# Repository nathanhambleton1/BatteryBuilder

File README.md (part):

# Battery Builder

A MATLAB app for lithium-ion cell test data. It has three tabs:

| Tab | What it does |
|---|---|
| **Plot** | Look at the test: cursor read-out, fit buttons, drag-to-zoom, middle-mouse pan. |
| **Load profile** | Shows the test's current profile and saves it to the workspace for a Simulink *Controlled Current Source*. |
| **Modeling** | One button pulls every parameter it can out of the test and fills in the boxes for the Simscape **Battery (Table-Based)** block. Empty boxes tell you what you still need from the datasheet. A second button saves everything to the workspace. |

Building the Simulink model is up to you; this app produces the workspace variables it needs. **Extract** fits the tables to the whole test so that a Battery (Table-Based) block reproduces it: on the sample 0 °C file **20 mV rms** in Simulink, the right starting voltage, and every discharge stopping at the cut-off. See §14.

**Presentation + video:** [`Modeling_Tab_Presentation.pptx`](Modeling_Tab_Presentation.pptx) (66 slides, Century Gothic, MATLAB charts as movable pictures, speaker notes) and [`Modeling_Tab_Presentation.mp4`](Modeling_Tab_Presentation.mp4) (the same deck presented with a voice-over, about an hour) explain how every Modeling-tab value is calculated from the charge and discharge cycles, why each method was chosen, and how to set up the thermal mass and h·A for the Simulink convection block. See §13.

---

## 1. Quick start

```matlab
cd 'C:\App Projects\BatteryBuilder'
BatteryDataBuilder                    % opens the app
BatteryDataBuilder('cell_25C.csv')    % opens it with a file already loaded
```

1. **Open CSV...** → pick one test file (one cell; charges at 25 °C, discharges at the test temperature).
2. **Plot** tab: look at the data.
3. **Load profile** tab: **Save load profile to workspace** → `batt_load`, `batt_stopTime`, `batt_Ts`, `batt_ambient`.
4. **Modeling** tab: **1. Extract data from test**. Fill in any orange *Required* boxes from the datasheet, then **2. Save to workspace** → `batt_*`.
5. In Simulink, type the `batt_*` names into the Battery (Table-Based) block (hover over any box to see where each one goes).

Requirements: MATLAB R2021a or newer. No toolboxes are needed for the app itself. Simscape Battery (or Simscape Electrical) is only needed for the Simulink model you build afterwards.

---

## 2. Files

```
BatteryDataBuilder.m              <- the app. Builds the window and the three tabs.
src/
  plotTab.m                   Tab 1 - interactive plot
  loadProfileTab.m            Tab 2 - current profile -> workspace
  modelingTab.m               Tab 3 - parameter boxes, Extract / Save buttons
  blockParameterList.m        the list of boxes on Tab 3 (variable names, where they go, datasheet hints)
  extractCellParameters.m     all the calculations (capacity, SOC, OCV, R0, RC pairs, thermal)
  explainParameter.m          the "How?" pop-up windows
  batterySources.m            the published sources behind each method (links shown in the "How?" windows)
  fitTableBased.m             Extract step 2: the tables fitted to the whole test (one least-squares solve) - §14
  simulateTableBased.m        the Table-Based block's equations in plain MATLAB (the fit and "Fit vs data")
  refineTimeGrid.m            splits long sample intervals (<= 0.2 % SOC) so the fit integrates like Simulink
  showTableFit.m              the "Fit vs data" window
graphs/                       PNGs: C-rate graphs (Load profile tab) and the fit check
plots/                        PNGs saved by the Plot tab's "Copy plot to a figure"
  loadBatteryCsv.m            reads a cycler CSV
Modeling_Tab_Presentation.pptx   the presentation (§13)
Modeling_Tab_Presentation.mp4    the presentation, narrated (§13)
```

`BatteryDataBuilder.m` adds `src/` to the path itself, so you never need to touch the other files to use the app.

How the pieces talk to each other:

```
BatteryDataBuilder.m
   | Open CSV  -> loadBatteryCsv(file) -> d (dataset)
   |              d is handed to every tab: plotTab.setData(d), loadProfileTab.setData(d), modelingTab.setData(d)
   |
   +-- plotTab          (only displays d)
   +-- loadProfileTab   (d.t, d.I, d.Tch -> batt_load, batt_stopTime, batt_Ts, batt_ambient)
   +-- modelingTab      Extract -> extractCellParameters(d, nRC, SOC_vec) -> R
                        R fills the boxes; "How?" -> explainParameter(key, R)
                        after Extract, d gains a 'SOC (-)' column which is sent back to the Plot tab
```

---

## 3. Test data format

One CSV per test. Column names are matched loosely (case, spaces and punctuation are ignored) and their order does not matter:

```
Record#  Step  TestTime (s)  StepTime (s)  Capacity (Ah)  Energy (Wh)
Current (A)  Voltage (V)  State  ES  DateTime  Temp 1  Chamber Temperature (C)
```

| Column | Used for |
|---|---|
| TestTime (s) | time axis (`DateTime` is the fallback). `hh:mm:ss` and `1d 02:03:04` strings are accepted. |
| Current (A), Voltage (V) | everything |
| State (C / D / R) | sign of the current when the cycler logs a positive magnitude, and rest detection |
| StepTime (s) | the exact moment the current switched, for R0 and the RC fits |
| Temp 1 | cell temperature: thermal fit and initial temperature |
| Chamber Temperature (C) | ambient for the thermal fit (and `batt_ambient`), and the test temperature label: the median chamber temperature **during the discharges** (§7.0) |

### Current sign: positive = charge

Everywhere in the app, and in every saved variable, **positive current = charge (into the cell) and negative = discharge**. The loader works out which way round your file is:

* If there is a State column, it compares the sign of the current in C and D rows, or uses State to give a sign to a magnitude-only current.
* If there is no State column, charging current must make the voltage rise (checked with dV/dt).

The top bar of the app shows which case was found (e.g. *"magnitude in file, sign taken from the State column"*).

---

## 4. Tab 1: Plot

| Control | Action |
|---|---|
| X axis / Left Y / Right Y | Pick columns. Ctrl+click picks several. A right axis is shown when something is selected there. Changing any of them redraws and fits the view to every curve straight away. **(none)** at the top of a Y list leaves that axis empty. |
| **Load twin from workspace** | Adds the digital-twin signals at the bottom of both Y lists, under a separator (see below). Press again after a new simulation run. |
| **Same units -> same Y scale** | On by default. When every curve on the left **and** the right has the same unit, both Y axes get the same limits, so e.g. measured voltage (left) and twin voltage (right) lie on top of each other. The lock holds through every zoom, pan and fit. The box shows `(locked: V)`, or `(units differ)` when it cannot apply. Untick it to give each side its own scale again. |
| **Fit all** | Show all the data. |
| **Fit horizontal** | Full X range, keep the Y zoom. |
| **Fit vertical** | Fit Y to the data inside the X range you are looking at. |
| Drag drop-down | Left-drag zooms to a box, X only, Y only, or is off. |
| **Left-drag** | Zoom into the dragged box. |
| **Middle-drag** (or Shift+left-drag) | Pan (move the view around). |
| Scroll wheel | Zoom in / out around the mouse. |
| Double-click | Fit all. |
| Right-click / **Zoom back** | Undo the last zoom or pan. |
| **Cursor** | A vertical line follows the mouse. Every curve gets a marker where the line crosses it, with its value in a label right next to the crossing. Labels move up and down with the curves, are pushed apart when they would overlap, and flip to the left side near the right edge. If the X column goes back and forth (e.g. Voltage vs SOC), the nearest point on screen is used instead. |
| **Copy plot to a figure** | A normal MATLAB figure of the current view, for saving or printing (legend bottom-left). It is also saved straight away as `plots/<csv name>.png` (overwritten by the next copy of the same file). |
| Keys | `f` = fit all, `Backspace` = zoom back, `Esc` = cancel a drag. |

### Twin vs measured

Log the twin with To Workspace blocks named `twin_soc`, `twin_current`, `twin_voltage` and `twin_temp` (format **Timeseries** or **Structure With Time**; *Array* also works together with `tout`). They are read from the base workspace, or from `out` when the model uses "Single simulation output". They show up as `Twin: SOC (-)`, `Twin: Current (A)`, `Twin: Voltage (V)`, `Twin: Temp (°C)`, drawn dashed. The twin's time starts at 0 like `batt_load`, so it lines up with the test on any X column (time columns are extended past the end of the test). A temperature above 150 is taken to be kelvin and converted to °C; an SOC above 1.5 is taken to be percent.

Each twin signal has a measured partner: SOC ↔ `SOC (-)` (after Extract), current ↔ `Current, +charge (A)`, voltage ↔ the file's voltage column, temperature ↔ the cell temperature column (`Temp 1`). With both shown and the **Cursor** on, a yellow label on the other side of the cursor line shows `Δ = twin − measured` at the cursor position. When there is no room on that side (the cursor is near an edge), the label moves below the value labels instead.

**Comparing twin and measured.** Two ways, both on one scale:
* Put both in the **same** list (Ctrl+click), e.g. `Voltage (V)` and `Twin: Voltage (V)` on the left. That leaves the right axis free for something else, such as current.
* Or put one on each side, e.g. `Voltage (V)` left and `Twin: Voltage (V)` right. With **Same units -> same Y scale** ticked, the right axis copies the left one.

The unit is the text in the last brackets of the name (`Voltage (V)` → V); the temperature columns count as °C. A twin signal counts as having its measured partner's unit, so `Temp 1` and `Twin: Temp (°C)` lock together too (`unitKey`, `updateLock` in `plotTab.m`).

Extra columns added for plotting: `Test Time (h)`, `Current, +charge (A)`, `Power, +charge (W)`, `Net Ah in (Ah)`, and after an extraction `SOC (-)`.

The tab keeps **one** axes for its whole life, with both Y axes created up front; the right ruler is only hidden when nothing is picked for it. On every change the old lines are deleted, the new ones drawn, the view fitted, and ~0.25 s later the limits are applied once more and the axes repainted (`refreshPlot`, `repaintSoon`). Earlier versions deleted and re-created the axes on each change, which sometimes left the right-axis curves undrawn until a click or **Fit all** forced a repaint.

Pan is implemented in `plotTab.m` → `onMouseDown` (`SelectionType == 'extend'`, which is what MATLAB reports for the middle button) and `onMouseMove`, which turns the mouse movement in pixels into data units using the axes' size in pixels.

---

## 5. Tab 2: Load profile

The plot shows the current over the whole test: green = charge (+), orange = discharge (−).

**Save load profile to workspace** writes:

| Variable | Contents |
|---|---|
| `batt_load` | `[t I]`, N×2. Time in seconds from 0, current in A, **+ = charge**. |
| `batt_load_ts` | the same data as a `timeseries` |
| `batt_stopTime` | length of the test (s): set the model **Stop time** to `batt_stopTime` |
| `batt_Ts` | the test's sampling interval (s, the median spacing of the time stamps): use it as the To Workspace **Sample time** (or a fixed-step solver's step size) so the twin is logged like the real test |
| `batt_ambient` | `[t T]`, N×2: the **chamber temperature in kelvin** on the same time points as `batt_load`, for the battery's thermal port. Missing readings are bridged linearly. Not written (and the list says why) if the file has no chamber temperature column. |
| `batt_ambient_ts` | the same as a `timeseries` |

The list under the button shows these values, plus the test's shortest and longest logging interval (cyclers often log faster during pulses than during rests, which is why the median is used).

### Pulse labels

Every charge and discharge pulse (a run of current with one sign) is labelled with:

* its **C-rate**, `|I| / AH`: the level it spends most of its time at (`CC`), the CC current of a tapering charge (`CC-CV`), or the average and peak for a varying load (`avg …C, max …C`);
* the **Ah** that went in (`+`) or came out (`−`) during that pulse: `Σ I·Δt / 3600`.

The C-rate needs the capacity: press **Extract** on the Modeling tab (or type an AH there) and the labels update. Until then the labels show amps. Labels that would overlap are hidden, biggest pulses first; zoom in to see the rest (`findPulses`, `layoutLabels` in `loadProfileTab.m`).

### Using it in Simulink

```
From Workspace  ->  Simulink-PS Converter  ->  Controlled Current Source  ->  Battery (Table-Based)
 Data: batt_load       output unit: A           + (arrow head) -> battery +
 Interpolate: on                                -               -> battery -
 Final value: Holding final value
```

With the source wired head-to-battery-plus, a positive signal pushes current **into** the battery, which is charging. That matches the sign of `batt_load`.

Thermal port (block option *Thermal model* = lumped thermal mass):

```
From Workspace  ->  Simulink-PS Converter  ->  Controlled Temperature Source  ->  Convective Heat Transfer  ->  Battery port H
 Data: batt_ambient    output unit: K           port A -> Thermal Reference        Area = 1 m^2
 Interpolate: on                                port B -> Convective block A       coefficient = batt_hA
```

Kelvin is used so the Simulink-PS Converter needs no affine (°C) conversion. A chamber that holds one temperature makes `batt_ambient` almost flat, but it still carries the real drift of the test, which the thermal fit (§7.7) used too.

Every logged current holds until the next sample, exactly like the cycler's own Ah counter. `buildProfile` (in `loadProfileTab.m`) therefore inserts one extra point 1 ms before **every** change of current, carrying the *old* current. With *Interpolate data = on*, the signal then steps exactly like the real test instead of ramping between two samples. (Ramping through the tapering current of a CV charge used to add 0.14 % SOC per charge in Simulink, §14.2.)

---

## 6. Tab 3: Modeling

### The walk-through

1. **1. Extract data from test**: runs `extractCellParameters` on the loaded file. Every box it can calculate turns green (**✓ From data**).
2. Boxes it could not calculate stay empty:
   * **Required** (orange): the block needs it. Type it in from the datasheet.
   * **Optional** (grey): leave it empty if you don't have it.
   * Hover over the status to see *why* it could not be found (e.g. *"no cell temperature column in the file"*) and what to look for on the datasheet.
3. Any box can be typed into: a number, a vector like `[0.02 0.021 0.022]`, or `0:0.1:1`. Typed values show as **Entered by you** (blue) and are never overwritten by Extract.
4. **How?** (on green boxes) opens a window that walks through the calculation step by step: what the parameter means in the block, the equations (rendered in LaTeX), the actual numbers from your file plugged into them (a worked example), the final table, and plots of the data it came from.
   A box whose cross-check failed shows **⚠ Check** instead of ✓ (e.g. AH vs the cycler's own Capacity column, or SOC0 vs the voltage).
5. **2. Save to workspace** writes every filled box as its `batt_*` variable and tells you which required boxes are still empty.

**Hover over any box** to see its workspace variable name and exactly where it goes in the block dialog.

### Block set-up this app assumes

These options stay the same as before; set them once in the block dialog:

| Block option | Setting |
|---|---|
| Charge dynamics | the **Charge dynamics (RC pairs)** drop-down on the tab (1, 2 or 3; default 3, the third pair is the hours-long recovery after a discharge, §14). Saved as `batt_nRC`. |
| Tabulate parameters over temperature | **Yes** when the file has two temperatures (charges at 25 °C, discharges at T ≠ 25 °C): Vector of temperatures T = `batt_T_vec` (K), and V0, R0, R1.., tau1.. are SOC × T matrices. **No** for the 25 °C file (one temperature, the tables are vectors). The tab shows which one. |
| Current directionality | **No** |
| Thermal port | **Model** |
| Expose SOC port | **Yes** |
| Self-discharge | Disabled. Enable it only if you fill in `batt_Rleak`. |
| Fade / calendar aging | Disabled |
| Extrapolation method | Nearest |

### The boxes

| Box | Variable | Block dialog | From the data? | If not: datasheet |
|---|---|---|---|---|
| SOC breakpoints | `batt_SOC_vec` | Main › Vector of state-of-charge values | your choice (default 31 points, dense at the knee and the top: `[0 .005 .01 .02 … .05 .075 .1:.05:.9 .925 .95 .97 .98 .99 1]`) | n/a |
| Temperature breakpoints T | `batt_T_vec` | Main › Vector of temperatures, T (K) | the chamber during the discharges and during the charges, when they differ by > 3 K (§7.0) | n/a (empty = one temperature) |
| Open-circuit voltage V0(SOC,T) | `batt_V0_vec` | Main › Open-circuit voltage, V0(SOC,T) | zero-current line through the discharges at several rates; long rests at the two ends | OCV-vs-SOC curve. **Required.** |
| Terminal voltage range | `batt_V_range` | Main › Terminal voltage operating range [Min Max] | min / max measured | cut-off voltages. Optional. |
| Terminal resistance R0(SOC,T) | `batt_R0_vec` | Main › Terminal resistance, R0(SOC,T) | first sample after each step from a rest | DC internal resistance. **Required.** |
| Cell capacity AH | `batt_AH` | Main › Cell capacity, AH (A*hr) | full CC-CV → discharge to cut-off | rated capacity. **Required.** |
| Self-discharge resistance | `batt_Rleak` | Main › Self-discharge resistance, Rleak | never (needs weeks of storage) | Optional |
| R1..R3(SOC,T), tau1..tau3(SOC,T) | `batt_R1_vec`, `batt_tau1_vec`, ... | Dynamics › polarization resistance / time constant | the first minutes after each step from a rest; R scaled to the measured R_dc at the other SOCs | rarely published. **Required** for the pairs in use. |
| Thermal mass | `batt_thermal_mass` | Thermal › Thermal mass (J/K) | cell temperature self-heating | mass × specific heat. **Required.** |
| Convection h·A | `batt_hA` | *not a battery parameter*: Convective Heat Transfer block, Area = 1 m², coefficient = `batt_hA` | cell temperature self-heating | depends on your fixture. Optional. |
| Initial SOC | `batt_SOC0` | Initial Targets › State of charge | SOC at the first sample | Optional |
| Initial cell temperature | `batt_T0` | Initial Targets › Cell temperature (K) | first cell-temperature reading | Optional |

A single number typed into an SOC-table box (e.g. one datasheet resistance) is copied to every SOC point when saved.

### What "no guessing" means here

* A box is only filled from the data if the data really contains what that value needs. Otherwise it stays empty and says why.
* There are **no** built-in default values. The old version's "assumed" fallbacks are gone.
* A capacity you type in is only used to build the SOC axis when the test has no complete full-to-empty discharge. The AH box then still shows **Entered by you**, not "From data".
* Between two measured SOC points a table is linearly interpolated. Beyond the measured SOC range the end value is held, which is what the block's *Nearest* extrapolation would do anyway. Every table entry is labelled in its **How?** window: `M` measured near that SOC, `I` interpolated, `E` end value held, `S` R1..R3 scaled so R0 + ΣR_k equals the R_dc measured at that SOC (§7.5). R0 itself is never scaled.
* Points taken while the cell was more than 3 K away from the chamber temperature (e.g. right after the 5.8C discharge) are left out of the tables: they belong to a different temperature.
* The OCV table is only filled if the data covers the whole SOC range. Past the data it extends at most 0.01 SOC.

---

## 7. How each value is calculated

All of this is in `src/extractCellParameters.m`, in the same order as below. Every method is tied to published work or MathWorks documentation; the tags in square brackets, such as [INL15], point to the reference list in §12. The same sources are listed, with links, at the bottom of every **How?** window (`src/batterySources.m`).

### 7.0 The model, and what your test can measure

The Battery (Table-Based) block [MW-TB], built on [Huria12], is an equivalent circuit: an OCV source, a series resistance R0 and up to three RC pairs, all as tables over SOC. Written with *i* = discharge current (positive):

```
V        = V0(SOC) − i·R0(SOC) − Σ_k R_k(SOC)·x_k        terminal voltage
dx_k/dt  = (i − x_k) / tau_k(SOC)                         current through RC pair k's resistor
SOC      = SOC0 − ∫ i dt / (3600·AH)                       coulomb counting
m·cp · dT/dt = i²·R0 + Σ_k R_k·x_k² − h·A·(T − T_amb)      lumped thermal mass + convection
```

**Your test** is a rate test of about 70 h: 5 CC-CV charges and 5 discharges to the cut-off, with rests in between. Most files use 0.1C, 0.2C, 0.5C and 1C, then one fast discharge that varies from about 3C to 7C:

```
0.34C CC-CV charge → 0.1C discharge to cut-off → 0.34C CC-CV → 0.2C → 0.34C CC-CV → ~0.5C
                   → 0.34C CC-CV → 1C → 0.34C CC-CV → ~3-7C          (with rests in between)
```

**The chamber schedule.** One file = one test temperature T, but the chamber is not at T all the time:

```
25 °C : rest → CC-CV charge
   T  : (right after the charge) rest → discharge
25 °C : (right after the discharge) rest → next charge ...            and so on, 5 times
```

So every **discharge** runs at the file's temperature T and every **charge** runs at 25 °C. What that means for the extraction:

* **Test temperature label** (`d.T_C`, what the tables are "for") = the median chamber temperature over the *discharge* samples. The median over the whole file can land on 25 °C for a cold test, because about half the test is at 25 °C (`loadBatteryCsv.m`). The top bar says so when the chamber moves by more than 3 K.
* **Two table temperatures.** In a file that is not at 25 °C the tables are built at **both** chamber temperatures (`d.T_C` for the discharges, `d.T_chg_C` for the charges), each from the data taken with the cell within ±3 K of it (§7.10 `maxDT`). They are saved as SOC × T matrices with `batt_T_vec = [T_low T_high] + 273.15` K, for the block option *Tabulate parameters over temperature = Yes*. `extractCellParameters` runs the table part once per temperature; `R.byT{j}` is the full result for `T_vec(j)`, and every **How?** window for a table opens once per temperature.
  * **Test temperature (discharges):** R0 and the RC pairs from the start of each discharge (SOC 1, after the 3 h rest at T), OCV and R_dc from the discharges at several rates. AH, SOC, SOC0 and the thermal values come from here too (AH is one number in the block).
  * **25 °C (charges):** R0 and the RC pairs from the start of each charge (near SOC 0, after the rest back at 25 °C), R_dc from the CC part of the charges (§7.5). There are no discharges at 25 °C, so V0 at 25 °C is the test temperature's V0 (the OCV changes only a few mV over 25 K). A table that cannot be measured at one temperature is copied from the other one so the block gets a full matrix, and its note says **COPIED**.
* **In the 25 °C file** everything is at 25 °C: one temperature, and the steps from rest at SOC 1 (discharges) and near SOC 0 (charges) both count.
* **What is NOT used: the rests after a step.** After a discharge the chamber goes back to 25 °C straight away, so the cell warms by ~25 K during that rest; after a charge it cools to T. The relaxation there is mixed with the temperature change, and fitting RC pairs to it gave nonsense (R1 of ~900 mΩ, tau at its 3000 s limit, worse with every extra pair). The start of each step is taken after a 3 h rest at a steady temperature, sampled from 0.05 s on, so that is where the dynamics are measured.
* **Thermal fit and `batt_ambient`** use the chamber column as it is, steps and all, so the 25 ↔ T switching is in the heat balance and in the Simulink ambient. `batt_T0` is the first cell reading (≈ 25 °C, because the chamber starts at 25 °C), which is the right start for a simulation driven by `batt_ambient`.

That decides what can be measured, and where:

| Quantity | Where this test shows it | How (section) |
|---|---|---|
| AH | every discharge from FULL to the cut-off; the slowest one (0.1C) is used | 7.2 |
| SOC | everywhere, by coulomb counting from FULL | 7.3 |
| OCV | **the whole SOC range**: the same discharge at 4 rates is extrapolated to zero current | 7.6 |
| R_dc = R0 + R1 + R2 | **the whole SOC range**: the slope of the same fit | 7.6 |
| R0 on its own | only where the current **starts from a rest**: each discharge (SOC 1, at T), each charge (SOC ≈ 0 … 0.03, at 25 °C) | 7.4 |
| R1, R2, tau1, tau2 on their own | the first minutes after those same steps | 7.5 |
| m·cp, h·A | the 5.8C discharge heats the cell, which then cools in the rest | 7.7 |

So in the middle of the SOC range the **sum** R0 + R1 + R2 is measured, but not how it splits between them: the current never starts from a rest there. The tables are built to respect that (§7.5, the `S` flag), and nothing is filled in from outside the file.

### 7.1 Phases
The current is split into runs of **charge** (I > 0), **discharge** (I < 0) and **rest** (I = 0). Back-to-back steps of the same kind merge, so a CC step plus a CV step is one charge phase (`findPhases`).

A charge phase is a **CC-CV charge** when its current has tapered below 35 % of its maximum while the voltage over the taper stayed within 15 mV. That flat voltage is the CV voltage (`cvPhases`).

### 7.2 Capacity `batt_AH`
* **FULL** = the end of a CC-CV charge at the highest CV voltage.
* **EMPTY** = the end of a discharge that is at least 5 minutes long, stopped at the cut-off, *and* ended on the end-of-discharge knee: over its last 3 % the voltage falls more than 3× faster per Ah than over its middle half (`endsAtKnee`). The cut-off is the lowest **end** voltage of all long discharges, so a short pulse that dips below the cut-off cannot move it. The knee check stops a partial discharge, like one HPPC step, from being mistaken for empty.
* `AH = Ah_in(FULL) − Ah_in(EMPTY)` with `Ah_in = Σ I·dt / 3600` (zero-order hold).
* **Which discharge:** your test has five FULL→EMPTY discharges. A faster discharge reaches the cut-off sooner because more voltage is lost over the resistance, so it delivers fewer Ah. The **slowest (0.1C)** comes closest to the charge actually stored and is the one used. The AH **How?** window lists all five as a rate-capability table.
* **Cross-check:** if the file has its own `Capacity (Ah)` column, the same discharge is added up from it too (`fileCapacity`; the column restarts at 0 on every step). The two should agree within ~1 %; more than 2 % apart marks the box **⚠ Check**.

*Sources:*
* [INL15] §3.2: the static capacity test is a constant-current discharge from fully charged to the minimum voltage, after a rest.
* [Barai19] §2: the capacity tests in the standards, and the fact that the measured capacity depends on the C-rate (impedance and heating).
* [Lin14]: capacity is the charge between 100 % (end of the CV charge) and 0 % (end of discharge).

### 7.3 SOC and `batt_SOC0`
Coulomb counting that resets to SOC = 1 at every FULL point: `SOC = 1 + (Ah_in − Ah_in(FULL)) / AH`. This is the same SOC definition the block uses [MW-TB]. Before the first full charge the same line is run backwards, so

```
SOC0 = 1 − (Ah put in between the first sample and the first FULL point) / AH
```

If it took almost a whole AH to fill the cell, the file started almost empty, and SOC0 is close to 0. That is normal when a test starts on a cell left at its cut-off: once the current stops, the voltage of a lithium-ion cell recovers to ~3.1–3.3 V even though it is empty.

After a fast discharge (1C, 5.8C) the cell hits the cut-off with charge still in it. SOC keeps counting with the 0.1C AH, so it correctly shows e.g. SOC 0.1 there, not 0.

**Cross-check against the voltage** (`socVoltageCheck`):
* The relaxed voltage of the first rest (the rest the file starts in, or else the first ≥ 10 min rest) is read backwards through the OCV table and compared with the coulomb-counted SOC at that moment.
* For comparison, the window also shows the voltage the cell relaxed to after the discharge to cut-off (SOC 0 by definition).
* A difference of more than 0.08 marks the box **⚠ Check**. So does a difference larger than the check's own uncertainty: 5 mV divided by the local OCV slope, which is large on flat curves such as LFP.

*Sources:*
* [Chang13]: coulomb counting ("book-keeping") and its error sources. It needs a known starting point (here FULL) and an accurate capacity (here §7.2).
* [Lin14]: the same 100 % / 0 % definition.

### 7.4 R0 `batt_R0_vec`
At every charge or discharge that starts after a rest of at least 10 min (`findOnsets`):

```
R0 = (V_first − V_rest) / I
```

* **V_rest** is the last rest sample. After a rest the voltage is steady and every RC pair is empty, so nothing but R0 explains the jump.
* **V_first** is the first sample after the switch. The cycler logs it 0.03–0.05 s after the switch (the `StepTime` column says exactly when); an RC pair's capacitor has no time to charge in that. Steps whose first sample is more than 1 s after the switch are not used.
* **I** is the step's constant current (median of its first samples), not the first reading: the first reading can spike. In the sample cycle the 0.1C step logs 0.343 A for one sample of a 0.265 A step, while its voltage drop (12.4 mV) matches 0.265 A. With the set current every rate gives 44–47 mΩ; with the spike the 0.1C step would give 36 mΩ.
* **Temperature.** A step is used for the table of the temperature the cell was at (within 3 K).
* **To the table.** The median of the steps at each SOC (`gridPoints`), straight line between SOCs, end values held. A rate test only starts from rest at one SOC per temperature, so in practice R0 is one number per temperature, held over SOC. R0 is **not** scaled anywhere: the extra resistance a constant current feels (R_dc − R0) goes to the RC pairs (§7.5).
* **Check by hand** (sample cycle, 0 °C, 0.5C): 4.18296 → 4.12360 V at 1.325 A → R0 = 44.8 mΩ. At 25 °C (charge from rest): 3.0962 → 3.1164 V at 0.8835 A → 22.9 mΩ.
* **Current dependence.** At 0 °C the 15 A (5.8C) step gives 35 mΩ against 44–47 mΩ for 0.1–1C: the cell's resistance falls as the current rises. The block has one R0, so the median is used, and the R0 **How?** window lists every step so you can see it.

*Sources:*
* [INL15] §4.4.2, eq. 4: R = ΔV/ΔI across the pulse edge.
* [MW-Char]: R0 from the sudden voltage change at a pulse.
* [Schweiger10]: the current-step method compared with AC and EIS methods.
* [Lin14]: R_s from the initial voltage jump.

### 7.5 RC pairs `batt_R1_vec`, `batt_tau1_vec`, ...
Measured on the **same steps from rest** as R0 (`fitDynamics`, `fitCluster`). The current is constant and every RC pair starts empty, so the block's voltage after the step is

```
V(t) = V_rest + I·[ R0 + Σ_k R_k·(1 − exp(−t/tau_k)) ] + s·I·t/3600
```

with `s` the OCV slope (V per Ah: the OCV moves as charge goes in or out). Divided by I this is the resistance the cell shows t seconds after the step, `(V − V_rest)/I`, which the R1 **How?** window plots straight from the data (log time axis) with the fit on top.

* **Window.** The first 600 s after each step, at most 1 % of SOC (so the OCV is close to a straight line), constant current, cell within 3 K of its temperature at the step, rates up to 2C.
* **Fit.** All steps at the same SOC (within 0.03) are fitted together. They share the time constants tau_k and the OCV slope s (same cell, same SOC); **each step gets its own R_k**. For given tau_k everything else is linear (R_k, s ≥ 0, `lsqnonneg`). The tau_k are searched on a log grid (0.5 s up to half the longest window, at least 2× apart), then refined with `fminsearch`. Each step gets the same weight, in ohms.
* **Why R_k per step.** At 0 °C the steps from the sample cycle do not agree: 100 s after the step the cell shows ~180 mΩ at 0.1C but ~115 mΩ at 1C. The cell's resistance falls with current; a linear block cannot do that. Forcing one R_k on every rate left 5–34 mV of error per step; sharing only the tau_k and letting R_k follow each step leaves 0.4–6 mV. The table takes the **median** R_k of the steps.
* **How many pairs.** The fit is always run with 1, 2 and 3 pairs and the RC **How?** window lists the rms error of each. More pairs can only lower it, and the window says so when a pair hardly helps. Sample cycle, 0 °C: 9.0 / 4.0 / 3.5 mV; 25 °C: 2.6 / 0.65 / 0.36 mV. A pair the fit leaves empty (R = 0 at every step) is reported as *not resolved – use fewer RC pairs*, never filled in.
* **From one SOC to the whole table: R_dc.** The steps are at one SOC, but the total resistance a constant current feels once the pairs are full,

  ```
  R_dc(SOC) = R0 + Σ_k R_k
  ```

  is measured at almost every SOC: at the test temperature from the discharges at several rates (§7.6), at 25 °C from the CC part of the charges, `R_dc = (V_charge − V0(SOC)) / I` (`chargeRdc`; V0 is the table itself, linear between breakpoints as the block uses it). At every breakpoint with an R_dc, all R_k are scaled by **one** factor `f = (R_dc − R0) / Σ R_k,step` (flag `S`); tau_k and the split between the pairs stay as the step fit found them. Between the step SOC (f = 1) and the R_dc points, f goes in a straight line. R_dc at a breakpoint = the median of the 1 % SOC points nearest it (`gridMedian`).
* **25 °C R_dc and hysteresis.** The charge-side R_dc also holds the gap between the charge and discharge OCV, which the block does not model. With it the model charges at the measured voltage (the twin's charge voltage error in §9). It is the right resistance for charging at 25 °C, not for a 25 °C discharge, which this file does not contain.

*Sources:*
* [Lin14]: the voltage response fitted by least squares as a sum of exponentials; 1, 2 and 3 RC pairs compared.
* [MW-Char], [MW-HPPC]: MathWorks fits R_i, tau_i to the voltage segments around each pulse.
* [Hu12]: a comparison of 12 equivalent-circuit structures.
* [Jackey13]: fitting large lookup tables in layers.

### 7.6 OCV `batt_V0_vec` and R_dc: the multi-rate fit (`multiRate`)
1. **Wait until the RC pairs have filled up.** Once every RC branch current equals the discharge current, the block's equation (§7.0) becomes a straight line in *i*:
   ```
   V(SOC, i) = V0(SOC) − i · R_dc(SOC),     R_dc = R0 + R1 + R2
   ```
   A sample is used once what is left of each RC transient, `R_k·i·exp(−t/tau_k)`, is below 1 mV. R_k and tau_k come from the **3-pair** fit of the steps at SOC 1 (§7.5), whatever number of pairs you pick, so the OCV and R_dc do not change with the RC pair count. Sample cycle: 6, 8 and 10 min for 0.1, 0.2 and 0.5C.
2. **Line the discharges up on one SOC axis.** Each discharge starts from FULL, so its SOC is exact (§7.3). Its voltage is averaged in 1 % SOC bins; bins the data only partly covers are skipped.
3. **Fit a straight line per bin.** At each 1 % of SOC: voltage against current over the discharges at ≤ 2C, using only samples with the cell within 3 K of the chamber. **intercept** (i = 0) = V0 (discharge side); **slope** = R_dc. With 3 or more rates the scatter around the line is reported. In the sample cycle the 1C discharge warms the cell past 3 K (left out) and a third of the 0.5C one does; the 5.8C one is past 2C.
4. **Discharge side only.** The block has one OCV; the discharge-side one makes the discharges come out right. The charges at 25 °C get their own R_dc (§7.5), which takes up the hysteresis.
5. **The two ends.** The very top (still settling) and the very bottom have no line. There the voltage at the **end of every rest of at least 1 h** is used (`restOcvPoints`): after a full charge the cell rests at its SOC-1 OCV, after a discharge at the OCV of the SOC it stopped at. A smooth (pchip) curve joins them to the line (`ocvFromMultiRate`). The table is forced to rise with SOC. The rests after a discharge end at 25 °C (the chamber has gone back); the OCV changes only a few mV with temperature.

With fewer than two discharge rates from FULL there is no OCV from the data (the note says why): enter the datasheet curve.

*Sources:*
* [Petzl13]: low-current curves still carry overpotential; the true OCV is the zero-current value.
* [Yao18]: U = U_ocv(SOC) − I·R(SOC) over several discharge rates, giving R from their voltage difference.
* [Bussios24]: pseudo-OCV curves at several C-rates extrapolated to zero current.
* [Barai19] §3: pseudo-OCV from slow cycling.
* [INL15] §4.4.2: OCV from rest points.

**Honest note:** no single paper found does exactly this combination: a straight-line fit at each SOC over full discharges at several C-rates, intercept = OCV and slope = R_dc. Its pieces are all in the sources above, and the straight line itself is just the block's own voltage equation once the RC pairs have settled.

### 7.7 Thermal `batt_thermal_mass`, `batt_hA`
Lumped model of the cell in the chamber:

```
m·cp · dT/dt = Q − h·A · (T − T_chamber)
Q = I·(V − V0(SOC)) − Σ_k R_k·x_k·(I − x_k)          (I + = charge)
```

* **The first term** is the electrical power lost inside the cell: current times the gap between terminal voltage and OCV. This is the irreversible heat of Bernardi's energy balance [Bernardi85], used the same way in [Lin14]. It comes from the **measured** voltage, so it stays right when the 5.8C discharge has warmed the cell and its real resistance has dropped. I²R from the 25 °C tables would invent heat there.
* **The second term** takes out the power that is only being stored in the RC capacitors; it comes back as heat in the following rest. With the block's voltage equation, Q is then exactly the block's own heat `I²·R0 + Σ R_k·x_k²`, in the right moments.
* **Left out:** the reversible (entropic) heat I·T·dV0/dT. It needs the OCV at several temperatures, and the block leaves it out too.

**Fitting.** A least-squares fit on dT/dt (10 s grid, smoothed) gives a starting point. Then `m·cp` and `h·A` are refined so that the *simulated* temperature matches the measured one, which removes the bias from the smoothing (`fitThermal`, `simulateThermal`). This needs a cell temperature column, a chamber temperature column and at least 0.5 K of self-heating.

**Sanity checks:**
* m·cp ≈ cell mass × ~1 J/(g·K). [Maleki99] measured 0.96–1.04 J/(g·K) on an 18650.
* h = h·A / (cell surface area) should land in 2–25 W/(m²·K) for still air [Incropera]. More than that means the fixture (clamps, cables, tray) carries heat away too, which is fine: h·A describes *your* set-up.

*Sources:* [Bernardi85], [Lin14], [Forgez10] (lumped thermal model, heat capacity and h identified from measured temperatures), [Maleki99], [Incropera]. For the Simulink side: [MW-Conv] and [MW-CTS].

### 7.8 `batt_V_range`, `batt_T0`
Lowest and highest measured voltage; first cell-temperature reading in kelvin.

### 7.9 What your test needs for each value

| Value | Test must contain |
|---|---|
| AH, SOC0 | a CC-CV charge followed (later) by a discharge to the cut-off voltage |
| OCV + R_dc over the whole SOC range | **2 or more** CC discharges from FULL at different rates (≤ 2C), with the cell near the chamber temperature (your rate test) |
| R0 | a charge or discharge that starts after a rest ≥ 10 min, first sample ≤ 1 s after the switch |
| R_k, tau_k | the same steps, ≤ 2C. At other SOCs scaled to R_dc; at several SOCs on their own only with pulses from rest there (HPPC / GITT) |
| OCV ends | rests ≥ 1 h after the full charge and after the discharge to cut-off |
| thermal mass, h·A | `Temp 1` and chamber temperature columns, and visible self-heating (your 5.8C step) |

### 7.10 Fixed analysis settings
These were "Extraction settings" boxes in the old version. They are now fixed in `constants()` at the top of `extractCellParameters.m`:

| Constant | Value | Meaning |
|---|---|---|
| `vTol` | 0.02 V | tolerance when matching the CV / cut-off voltage |
| `minRestS` | 600 s | a step counts as "from rest" when the rest before it lasted this long |
| `maxEdgeDt` | 1 s | the first sample after the switch must be this close to it (R0) |
| `minStepC` | 0.08 C | smaller steps are not used |
| `onsetMaxS`, `onsetMaxDSOC` | 600 s, 0.01 | RC fit window after each step |
| `tauMin` | 0.5 s | shortest time constant (longest: half the window) |
| `clusterSOC` | 0.03 | steps closer than this in SOC are fitted together |
| `maxDT` | 3 K | data with the cell further than this from a table's temperature is not used for it |
| `mrMaxCrate` | 2 C | fastest step / discharge used in the RC and multi-rate fits |
| `settleV` | 1 mV | multi-rate fit: RC transient left over before a sample is used |
| `settleNoFit` | 1800 s | ... the wait instead, when there are no RC pairs |
| `ocvRestS` | 3600 s | rests at least this long give an OCV point (the ends of the curve) |

---

## 8. Code walk-through

### `BatteryDataBuilder.m`
Builds the window: title, **Open CSV...**, file info, and a tab group. It calls `plotTab`, `loadProfileTab` and `modelingTab` to fill the three tabs. Each returns a small `api` struct (`setData`, ...). `openFile` reads the CSV with `loadBatteryCsv` and hands the dataset to all three tabs. `onDataChanged` passes the SOC column from the Modeling tab back to the Plot tab. `fig.UserData.api` exposes the tab APIs for scripting and tests.

### `src/loadBatteryCsv.m`
`findCol` matches column names loosely. `toSeconds` / `toNum` handle numbers, durations and time strings. The function drops rows missing time/V/I, sorts by time, sets the test temperature label, fixes the current sign (positive = charge) and adds the plot columns.

### `src/plotTab.m`
All state (`series`, zoom stack, drag/pan state, cursor handles) lives in variables shared by nested functions.

| Function | Job |
|---|---|
| `refreshPlot`, `addSeries` | draw the chosen columns (left / right axes) |
| `fitView`, `extentOf` | Fit all / horizontal / vertical |
| `applyZoom`, `pushZoom`, `zoomBack` | zoom and its undo stack |
| `onMouseDown/Move/Up` | box zoom, middle-drag pan, cursor |
| `onScroll`, `onKey` | wheel zoom, keys |
| `buildCursor`, `updateCursor`, `interpMono` | cursor line, markers and labels |

The figure-level mouse callbacks only act while the Plot tab is the visible tab (`tabVisible`).

### `src/loadProfileTab.m`
`setData` draws the profile and the summary. `buildProfile` adds the step points. `findPulses` splits the current into charge / discharge pulses and `makeLabels` / `layoutLabels` put their C-rate and Ah labels on the plot. `onSave` writes `batt_load`, `batt_load_ts`, `batt_stopTime` and `batt_Ts`.

### `src/blockParameterList.m`
One entry per box: key, label, variable, block location, unit, group, required / optional, datasheet hint, RC pair number, and whether it is a per-SOC vector. **To add a box, add a row here** (and, if the data can give it, a key in `extractCellParameters`).

### `src/modelingTab.m`
`vals` holds each box's number and `src` says where it came from (`''`, `'calc'` or `'user'`).

| Function | Job |
|---|---|
| `onExtract` | run the extraction, then fill the green boxes and clear stale ones (user entries are kept) |
| `onEdit` | parse what you type |
| `refreshRows` | status text, colours and tooltips |
| `onSave` | write to the workspace; expand scalars; warn about missing boxes or length mismatches |
| `drawOverview` | the test overview and table plots on the right |

### `src/extractCellParameters.m`
The calculations, described in §7. `findOnsets` / `fitDynamics` / `fitCluster` (R0 and the RC pairs from the steps from rest), `multiRate` (the zero-current fit over the discharge rates), `chargeRdc` (R_dc from the charges), `buildTables` (onto the SOC breakpoints, scaled to R_dc) and `ocvFromMultiRate`. Returns `R.value`, `R.found`, `R.note`, `R.diag` (data for the pop-ups), `R.d` (dataset with SOC) and `R.report` (text summary).

### `src/batterySources.m`
The reference list (§12) and, per parameter, what each source supports. The **How?** windows show it as clickable links (`uihyperlink`).

### `src/explainParameter.m`
One `case` per parameter. The left side is a scrolling list of blocks built with four small helpers: `H` (heading), `P` (paragraph), `EQ` (an equation, shown with a LaTeX `uilabel`) and `M` (a monospaced table with the M/I/E flags). Each window explains what the parameter means, the model equations, the method step by step, and a worked example with this file's own numbers (e.g. `AH = Q_in(full) − Q_in(empty) = …`, an example step's (V_first − V_rest)/I, the R_k of every step and the rms error with 1, 2 and 3 pairs). The right side has one or two plots of the data itself: the raw samples around a step, `(V − V_rest)/I` after every step with the fit on top, every discharge on one SOC axis, V against current at one SOC.

---

## 9. Validation

**0. The sample cycle (`task.txt`).** A made-up file shaped exactly like the real 0 °C tests: 25 °C CC-CV charges, 3 h rests while the chamber moves, discharges at 0.1 / 0.2 / 0.5 / 1C and 15 A (5.8C) at 0 °C. The extracted tables were put through the block's own equations (`V = V0 + I·R0 + Σ R_k·x_k`, SOC from the coulomb count, the measured cell temperature to pick between the 0 °C and 25 °C columns) over the whole test, and compared with the measured voltage:

rms of twin − measured over SOC 0.05–0.95 (the knee and the very top are discussed below):

| RC pairs | 0.1C | 0.2C | 0.5C | 1C | 25 °C charges |
|---|---|---|---|---|---|
| **this version**, 1 / 2 / 3 | 6.8 / 6.8 / 6.8 mV | 9.1 / 9.1 / 9.1 mV | 26 / 26 / 26 mV | 135 / 135 / 135 mV | 5–9 mV |
| previous version, 1 | 12 mV | 34 mV | 94 mV | 85 mV | 51–52 mV |
| previous version, 2 | 237 mV | 435 mV | 841 mV | 1259 mV | 30–32 mV |
| previous version, 3 | 473 mV | 758 mV | 1463 mV | 2227 mV | 114–115 mV |

Over the middle of the SOC range the result hardly depends on the number of pairs: R_dc fixes what a constant current feels there, and the pairs only shape the first minutes after a step (where 1 / 2 / 3 pairs give 9.0 / 4.0 / 3.5 mV, §7.5). The previous version got **worse with every RC pair** (whole test 116 → 780 → 1126 mV rms), because it fitted the pairs to the rests in which the chamber was warming the cell by 25 K. What is left now:
* **1C**: the cell's resistance falls with current, and the cell warms to 11 °C; a linear block with one table cannot match every rate (§7.5).
* **Last few % of SOC**: the knee falls between the breakpoints 0 and 0.05. More breakpoints there (e.g. 0.02, 0.03) follow it more closely.
* **SOC 0.95–1**: the OCV curves sharply there; a breakpoint at 0.98 or 0.99 helps.
* **15 A**: the cell heats to 60 °C, far outside the 0–25 °C tables, so the twin is far off there. Only a test at that temperature can fix that.

Sections 1–3 were run on the **previous** version (RC pairs from the rests); they have not been re-run on this one. The extraction was validated on test files written from a cell with **known** parameters (a 2-RC cell with a lumped thermal mass, the same structure as the block). Each file is run through the extraction and compared with the truth. The validation scripts (`tests/runValidation.m`, `tests/makeSyntheticCellData.m`) are no longer in the repository; they are in the git history (commit `0cd3cc2`) if you want to re-run them.

**1. Your profile (the rate test).** `makeSyntheticCellData(dir, 25, 'rate')`:
* the cell starts nearly empty;
* 0.34C CC-CV charges alternate with 0.1 / 0.2 / 0.51 / 1 / 5.8C discharges to the cut-off, with 2 h rests (~53 h);
* there are no pulses at mid SOC;
* the 5.8C step heats the cell by ~25 K.

| AH | SOC0 error | OCV max error (all SOC) | R0+R1+R2 (SOC 0.05–0.95) | R0 | tau2 | m·cp | h·A |
|---|---|---|---|---|---|---|---|
| −0.8 % | 0.000 | 0.9 mV | 4.6 % | 9.5 % | 5.5 % | −2.8 % | +2.8 % |

The multi-rate fit used the 0.1–1C discharges. One step and one rest at the end of the 5.8C discharge were left out as too hot. Before the rate-test changes, the same file gave R0 about 50 % low at mid SOC (only interpolated, with a hot end point), so this is the change that matters for your data.

**1b. Your profile with the real chamber schedule.** `makeSyntheticCellData(dir, [25 10], 'chamber')`: charges at 25 °C, rest + discharge at T, 0.1 / 0.2 / 0.5 / 1 / 5C, 3.6 h rests, 69 h, the chamber following its set-point with a 10 min lag:

| file | label | OCV found | OCV max error | R0+R1+R2 (SOC 0.05–0.95) | AH | OCV charge side |
|---|---|---|---|---|---|---|
| 25 °C | 25.0 °C | yes | 1.0 mV | 4.6 % | −0.8 % | 0.34C charge |
| 10 °C | 10.0 °C | yes | 2.8 mV | 7.5 % | −0.8 % | none (charges at 25 °C) |

The synthetic cell does not reproduce the poorly defined post-CV rest fits that real data gives, so it cannot show the old 25 °C failure itself; it checks that the schedule is handled and that nothing else changed.

**2. An HPPC test** (rest, CC-CV, C/5 discharge, HPPC, dynamic load) at 25 °C and 0 °C, compared over SOC 0.1–0.95:

| | AH | SOC0 | OCV max error | R0 | R1 | R2 | tau1 | tau2 | m·cp | h·A |
|---|---|---|---|---|---|---|---|---|---|---|
| 25 °C | −1.3 % | 0.501 (error 0.000) | 3.1 mV | 1.2 % | 2.8 % | 1.7 % | 1.5 % | 0.5 % | +9.2 % | +0.7 % |
| 0 °C | −1.5 % | 0.500 (error 0.000) | 2.0 mV | 1.8 % | 3.4 % | 3.3 % | 1.3 % | 1.7 % | +2.6 % | +0.2 % |

This file has only one full discharge, so it uses the older OCV method. Its few-mV OCV error ends up in the heat estimate I·(V − OCV) over many hours, hence m·cp +9 %. The AH difference is because the capacity is measured down to the test's cut-off voltage at C/5, as defined in §7.2.

**3. No guessing.** A file cut down to 11 hours with no full discharge and no temperature columns must give AH, SOC, OCV, R, tau and the thermal values all **empty**. Typing in a datasheet AH then lets R0 and the RC pairs be calculated.

Synthetic data only proves the method recovers values that are really there. On real data the remaining differences come from things the synthetic cell does not have, such as hysteresis and a resistance that changes with rate. Each **How?** window shows the cross-checks:
* AH against the cycler's capacity column;
* SOC0 against the voltage;
* the scatter of the multi-rate straight-line fit;
* R0+R1+R2 against R_dc.

---

## 10. Troubleshooting

| Symptom | Cause / fix |
|---|---|
| "Could not find Current and Voltage columns" | Header names too different. Add your names to the `findCol` patterns in `loadBatteryCsv.m`. |
| Current sign looks wrong | Check the sign note in the top bar. With no State column the sign comes from dV/dt. |
| AH stays empty | No CC-CV charge followed by a full discharge to cut-off. Type the datasheet capacity into the AH box and press Extract again: SOC, R0 and the RC pairs can then be calculated. |
| R1/tau1 empty | No charge / discharge starts after a rest ≥ 10 min with its first sample ≤ 1 s after the switch, at ≤ 2C. |
| R2 / R3 says *not resolved* | The steps cannot carry that many pairs: the fit leaves the extra pair empty. Choose fewer RC pairs. |
| OCV empty | The multi-rate fit and the long rests do not cover SOC 0..1. The OCV window's note says which part is missing. Use the datasheet OCV curve. |
| OCV empty in the 25 °C file only | Fixed: the multi-rate wait comes from the steps at SOC 1, not from the rests (§7.6 step 1). If it still happens, the OCV window names the discharge rate that never settled. |
| OCV note says "no multi-rate fit" | Fewer than 2 different CC discharge rates start from a full CC-CV charge, so there is no OCV from the data. Use the datasheet OCV curve. |
| `batt_ambient` not saved | The file has no chamber temperature column. Use a Constant block with the chamber temperature (K). |
| Thermal mass empty | No `Temp 1` / chamber column, or the cell heats by less than 0.5 K. Enter mass × specific heat. |
| Save warns about a length mismatch | You changed the SOC breakpoints after extracting. Press Extract again. |

---

## 11. Next steps (not in this version)

* More temperatures: combine several files (each already gives its test temperature + 25 °C) into one SOC × T table set.
* Separate charge / discharge R0 (Current directionality = Yes).
* Save / load a parameter set (.mat) from the Modeling tab.
* Optional automatic build of a test-bench Simulink model.

---

## 12. References

Each source was opened and checked in November 2026. **(free)** means readable without a subscription. For each one: what it is, and what this tool takes from it. The same list, with clickable links, is at the bottom of every **How?** window (`src/batterySources.m`).

**The block and MathWorks' own workflows**

* **[MW-TB]** MathWorks, *Battery (Table-Based)*, Simscape Battery block reference. <https://www.mathworks.com/help/simscape-battery/ref/batterytablebased.html> (free)
  It defines the model these tables go into: V0(SOC,T) lookup, R0(SOC,T), up to five RC pairs (R_k, tau_k), SOC by coulomb counting over the capacity, and a thermal mass heated by the resistive losses. It is the "what goes where" for every box.
* **[Huria12]** T. Huria, M. Ceraolo, J. Gazzarri, R. Jackey, "High fidelity electrical model with thermal dependence for characterization and simulation of high power lithium battery cells", IEEE IEVC 2012, doi:10.1109/IEVC.2012.6183271. [MathWorks PDF](https://jp.mathworks.com/content/dam/mathworks/tag-team/Objects/i/71900-ieee-2012-high-fidelity-lithium-battery-model-with-thermal-effect.pdf) (free)
  The MathWorks paper the Table-Based block is built on: an RC-ladder model with SOC- and temperature-dependent tables, identified from pulse-discharge tests.
* **[Jackey13]** R. Jackey, M. Saginaw, P. Sanghvi, J. Gazzarri, T. Huria, M. Ceraolo, "Battery Model Parameter Estimation Using a Layered Technique: An Example Using a Lithium Iron Phosphate Cell", SAE 2013-01-1547. [MathWorks PDF](https://it.mathworks.com/content/dam/mathworks/tag-team/Objects/s/76117-sae-2013-battery-estimation-layered-technique.pdf) (free)
  It fits large lookup tables in smaller pieces, as this tool does: one quantity at a time, at the SOC points where the data shows it.
* **[MW-Char]** MathWorks, *Characterize Battery Cell for Electric Vehicles* (example). <https://www.mathworks.com/help/simscape-battery/ug/battery-cell-characterization-for-ev.html> (free)
  R0 from the sudden voltage change at a pulse, and R_i / tau_i from fitting the relaxation segments. These are the R0 and RC methods here (§7.4, §7.5).
* **[MW-HPPC]** MathWorks, *Estimate Battery Model Parameters from HPPC Data* (example). <https://www.mathworks.com/help/simscape-battery/ug/estimate-battery-model-parameters-from-hppc-data.html> (free)
  MathWorks' HPPC workflow fits the relaxation after each pulse by default (§7.5).
* **[MW-Conv]** MathWorks, *Convective Heat Transfer*, Simscape block reference. <https://www.mathworks.com/help/simscape/ref/convectiveheattransfer.html> (free)
  Q = k·A·(T_A − T_B). With Area = 1 m² the coefficient is h·A directly, which is why `batt_hA` goes in that way.
* **[MW-CTS]** MathWorks, *Controlled Temperature Source*, Simscape block reference. <https://www.mathworks.com/help/simscape/ref/controlledtemperaturesource.html> (free)
  Sets a temperature from a physical signal. It is driven with `batt_ambient`, the chamber temperature (§5).

**Test methods**

* **[INL15]** J. P. Christopherson, *Battery Test Manual for Electric Vehicles, Rev. 3*, Idaho National Laboratory, INL/EXT-15-34184, 2015. <https://inldigitallibrary.inl.gov/sites/STI/STI/6492291.pdf> (free)
  * §3.2, static capacity test: a constant-current discharge from fully charged to the minimum voltage, after a rest (§7.2).
  * §4.4.2: resistance = ΔV/ΔI across a pulse edge (eq. 4) (§7.4), and OCV from the rest points (§7.6, the two ends).
* **[Barai19]** A. Barai, K. Uddin, M. Dubarry et al., "A comparison of methodologies for the non-invasive characterisation of commercial Li-ion cells", *Progress in Energy and Combustion Science* 72 (2019), doi:10.1016/j.pecs.2019.01.001. <https://www.osti.gov/pages/servlets/purl/1530390> (free)
  A review of the whole field:
  * §2: capacity tests, and capacity depending on the C-rate (§7.2);
  * §3: pseudo-OCV from slow cycling, with the charge/discharge average as the recommended compromise (§7.6);
  * §5: the instantaneous step is ohmic, and isolating it needs very fast sampling, so 1 s data also catches a little charge transfer (§7.4).
* **[Lin14]** X. Lin, H. Perez, S. Mohan, J. Siegel, A. Stefanopoulou, Y. Ding, M. Castanier, "A lumped-parameter electro-thermal model for cylindrical batteries", *J. Power Sources* 257 (2014) 1–11, doi:10.1016/j.jpowsour.2014.01.097. [Author PDF](https://public.websites.umich.edu/~annastef/papers_battery/Xinfan_JPS.pdf) (free)
  The closest single paper to this tool:
  * SOC by coulomb counting between the end of the CV charge and the end of discharge;
  * OCV as the average of a slow charge and discharge;
  * R_s from the voltage jump, and RC pairs from least-squares fits of the relaxation (1, 2 and 3 pairs compared);
  * a lumped thermal model with Q = I·(V_T − V_OCV), identified from measured current, surface and ambient temperature.
* **[Chang13]** W.-Y. Chang, "The State of Charge Estimating Methods for Battery: A Review", *ISRN Applied Mathematics* 2013, 953792, doi:[10.1155/2013/953792](https://doi.org/10.1155/2013/953792) (free)
  Coulomb counting and its error sources: a known starting point and an accurate capacity are needed (§7.3).
* **[Petzl13]** M. Petzl, M. A. Danzer, "Advancements in OCV Measurement and Analysis for Lithium-Ion Batteries", *IEEE Trans. Energy Conversion* 28(3), 2013, doi:[10.1109/TEC.2013.2259490](https://doi.org/10.1109/TEC.2013.2259490) (paywalled)
  Low-current OCV curves still carry overpotential; the true OCV is the zero-current value. This is the reason for extrapolating to i = 0 (§7.6).
* **[Yao18]** Q. Yao, D. Lu, G. Lei, "A Simple Internal Resistance Estimation Method Based on Open Circuit Voltage Test under Different Temperature Conditions", IEEE PEAC 2018, doi:10.1109/PEAC.2018.8590350. [Accepted manuscript](https://opus.lib.uts.edu.au/bitstream/10453/132782/5/A%20Simple%20Internal%20Resistance%20Estimation%20Method%20Based%20on%20Open%20Circuit%20am.pdf) (free)
  Discharges at several rates follow U = U_ocv(SOC) − I·R(SOC), so R comes from the voltage difference between the rates. This is the slope half of the multi-rate fit (§7.6).
* **[Bussios24]** M. Bussios, A. Goldar, E. Garone, M. Kinnaert, "Fast Determination of OCV Curve for Lithium-ion Batteries", European Control Conference 2024, doi:[10.23919/ECC64448.2024.10591299](https://doi.org/10.23919/ECC64448.2024.10591299) (paywalled; checked from the abstract)
  Pseudo-OCV curves at several C-rates (C/50 … C/5), extrapolated to zero current. They use a statistical fit; this tool uses a straight line in I, the block's own equation (§7.6).
* **[Schweiger10]** H.-G. Schweiger et al., "Comparison of Several Methods for Determining the Internal Resistance of Lithium Ion Cells", *Sensors* 10(6) (2010) 5604–5625, doi:10.3390/s100605604. <https://www.ncbi.nlm.nih.gov/pmc/articles/PMC3247723/> (free)
  The current-step method compared with AC, EIS and energy-loss methods (§7.4).
* **[Hu12]** X. Hu, S. Li, H. Peng, "A comparative study of equivalent circuit models for Li-ion batteries", *J. Power Sources* 198 (2012) 359–367, doi:[10.1016/j.jpowsour.2011.10.013](https://doi.org/10.1016/j.jpowsour.2011.10.013) (paywalled)
  Twelve equivalent-circuit structures compared: how many RC pairs are worth having (the Charge dynamics drop-down).

**Heat**

* **[Bernardi85]** D. Bernardi, E. Pawlikowski, J. Newman, "A General Energy Balance for Battery Systems", *J. Electrochem. Soc.* 132(1) (1985) 5–12, doi:[10.1149/1.2113792](https://doi.org/10.1149/1.2113792) (paywalled)
  The energy balance behind every battery thermal model. Its irreversible heat, I·(V − OCV), is the heat source in §7.7.
* **[Forgez10]** C. Forgez, D. V. Do, G. Friedrich, M. Morcrette, C. Delacourt, "Thermal modeling of a cylindrical LiFePO4/graphite lithium-ion battery", *J. Power Sources* 195(9) (2010) 2961–2968, doi:[10.1016/j.jpowsour.2009.10.105](https://doi.org/10.1016/j.jpowsour.2009.10.105) (paywalled)
  A lumped thermal model whose heat capacity and heat-transfer coefficient are identified from measured temperatures, as in §7.7.
* **[Maleki99]** H. Maleki, S. Al Hallaj, J. R. Selman, R. B. Dinwiddie, H. Wang, "Thermal properties of lithium-ion battery and components", *J. Electrochem. Soc.* 146(3) (1999), doi:10.1149/1.1391704. <https://www.osti.gov/biblio/345380> (free record)
  The measured specific heat of an 18650 cell is about 0.96–1.04 J/(g·K). Use it to sanity-check `batt_thermal_mass` against cell mass × cp.
* **[Incropera]** F. Incropera et al., *Fundamentals of Heat and Mass Transfer*, 6th ed., Wiley 2007, Table 1.1. [Course handout](https://pages.mtu.edu/~fmorriso/cm3120/typical_values_heat_transfer_coefficient.pdf) (free)
  Typical convection coefficients: free convection in gases 2–25 W/(m²·K), forced 25–250. A sanity check for h = `batt_hA` / cell area.

Also useful, but not checked online: G. Plett, *Battery Management Systems, Vol. I: Battery Modeling*, Artech House 2015 (ISBN 9781630810238). It is the standard textbook for equivalent-circuit models, OCV tests and coulomb counting.

---

## 13. The presentation and the video

* [`Modeling_Tab_Presentation.pptx`](Modeling_Tab_Presentation.pptx): 66 slides (slides 63–65 = the whole-test fit, §14; the video below covers the first 63), all text in Century Gothic. Every chart is a MATLAB figure inserted as a picture you can copy, move or resize. The arrows and labels on the charts are separate PowerPoint shapes (grouped per callout) that fade in on click, so they can be edited too. Slides use fade / push transitions. The speaker notes hold the full talk.
* [`Modeling_Tab_Presentation.mp4`](Modeling_Tab_Presentation.mp4): the same deck presented, about an hour, with a natural-sounding voice-over (Kokoro, an open-source neural text-to-speech model run locally). The callouts appear as the talk reaches them.

What it covers, in the order the extraction runs: the model and what a test can show; the CSV and the chamber schedule (charges at 25 °C, discharges at T) with the ±3 K window; phases, FULL and EMPTY (knee check); AH and the rate table; SOC, SOC0 and its voltage check; R0 at the current steps; the RC pairs from the rests (branch currents from the real history, how the fit is solved); the multi-rate fit (settle wait, the 25 °C OCV problem, the straight line per SOC, charge side and hysteresis, the two ends); how the tables are built (M / I / E / S); and the thermal side: the heat source, the m·cp / h·A fit, two checks you can do by hand (the first minute of the fast discharge gives m·cp; every chamber step gives τ_th = m·cp / h·A), the Simulink wiring of the battery thermal port and the Convective Heat Transfer block, and what to use when the thermal boxes are empty.

Every chart and number comes from a run of `extractCellParameters` on synthetic 10 °C and 25 °C files that follow the real profile and chamber schedule (~70 h, 0.1 / 0.2 / 0.5 / 1 / 5C). Because the synthetic cell's values are known, the deck also shows how close each result is.

---

## 14. Whole-test fit: making the Table-Based block reproduce the test

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
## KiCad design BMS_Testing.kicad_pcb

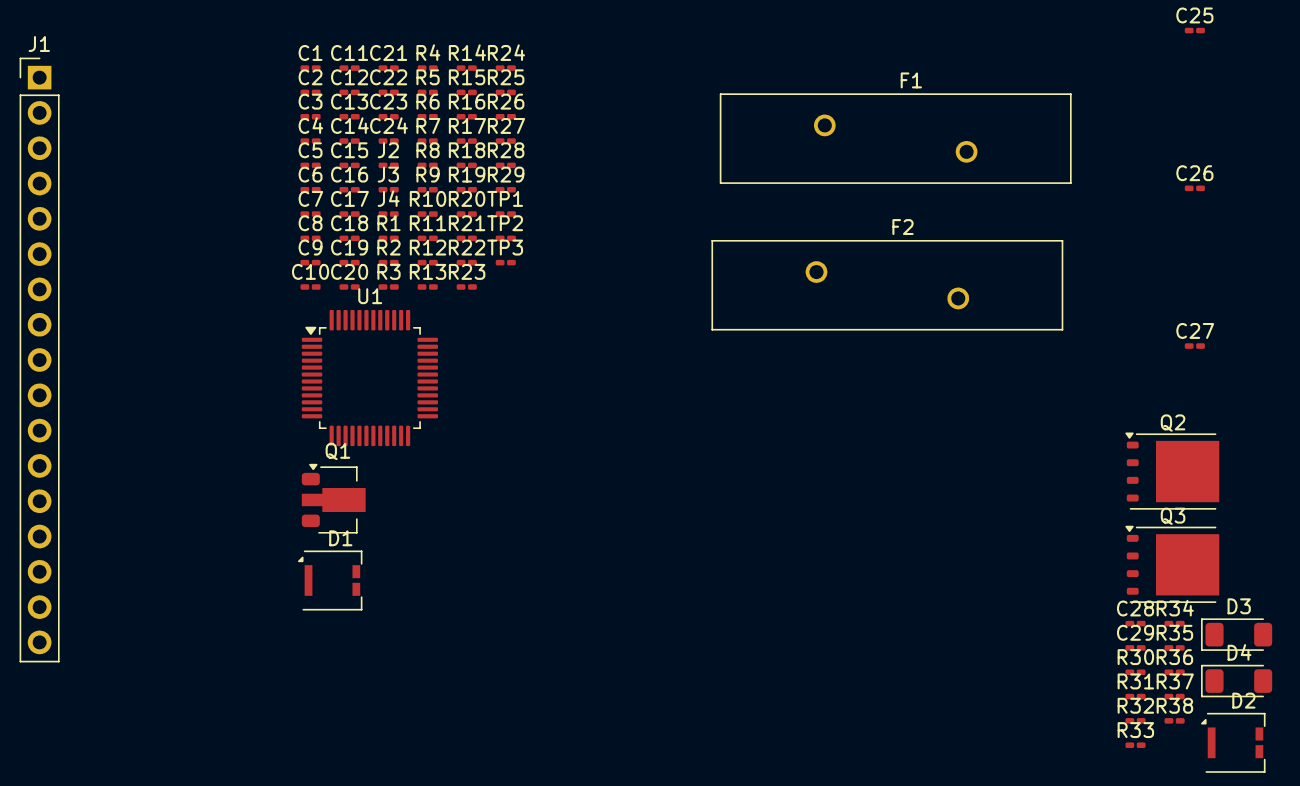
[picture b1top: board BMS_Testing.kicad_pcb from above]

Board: 2 copper layers, 84 parts (0 on the bottom side), 71 nets, no tracks yet.

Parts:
C1, C2, C3, C4, C5, C6, C7, C8, C9, C10, C11, C12, C13, C14, C15, C16, C17: 220nF; C_0201_0603Metric_Pad0.64x0.40mm_HandSolder
C18, C19, C28, C29: 0.1uF; C_0201_0603Metric_Pad0.64x0.40mm_HandSolder
C20, C21, C22, C24, C25: 1uF; C_0201_0603Metric_Pad0.64x0.40mm_HandSolder
C23: 22nF; C_0201_0603Metric_Pad0.64x0.40mm_HandSolder
C26: 100pF; C_0201_0603Metric_Pad0.64x0.40mm_HandSolder
C27: 0.47uF; C_0201_0603Metric_Pad0.64x0.40mm_HandSolder
D1, D2: 100V; Littelfuse_PolyZen-LS
D3, D4: BZV55B16; D_MiniMELF
F1, F2: Fuse; Fuse_BelFuse_0ZRE0200FF_L24.9mm_W6.1mm
J1: Voltage Taps; PinHeader_1x17_P2.54mm_Vertical
J2: Thermistor 1; R_0201_0603Metric_Pad0.64x0.40mm_HandSolder
J3, J4: Thermistor 2; R_0201_0603Metric_Pad0.64x0.40mm_HandSolder
Q1: NPN; SOT-89-3
Q2, Q3: CSD19532Q5B; TDSON-8-1
R1, R2, R3, R4, R5, R6, R7, R8, R9, R10, R11, R12, R13, R14, R15, R16, R17: 20; R_0201_0603Metric_Pad0.64x0.40mm_HandSolder
R18: 0.001; R_0201_0603Metric_Pad0.64x0.40mm_HandSolder
R19, R20, R30: 100; R_0201_0603Metric_Pad0.64x0.40mm_HandSolder
R21: 1K; R_0201_0603Metric_Pad0.64x0.40mm_HandSolder
R22, R31, R34: 10M; R_0201_0603Metric_Pad0.64x0.40mm_HandSolder
R23: 300; R_0201_0603Metric_Pad0.64x0.40mm_HandSolder
R24, R25, R26: 10k; R_0201_0603Metric_Pad0.64x0.40mm_HandSolder
R27, R28, R29: 1k; R_0201_0603Metric_Pad0.64x0.40mm_HandSolder
R32, R33, R35, R36, R37, R38: 5.1k; R_0201_0603Metric_Pad0.64x0.40mm_HandSolder
TP1: TS1; R_0201_0603Metric_Pad0.64x0.40mm_HandSolder
TP2: TS2; R_0201_0603Metric_Pad0.64x0.40mm_HandSolder
TP3: TS3; R_0201_0603Metric_Pad0.64x0.40mm_HandSolder
U1: BQ7695202PFB; TQFP-48_7x7mm_P0.5mm

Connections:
/1.8V: C24.1, U1.24 (REG18)
/4-6V Input: C23.1, Q1.3 (E), U1.36 (REGIN)
/SRN: C18.2, C19.2, R20.2, U1.20 (SRN)
/SRP: C18.1, C19.1, R19.2, U1.18 (SRP)
ALERT: R26.1, U1.25 (HDQ_IO/ALERT)
BAT+: D2.2 (A), F1.1, J1.17, R17.1
BAT-: J1.1, R1.1, R18.1, R19.1
BUS+: C28.1, D4.2 (A), Q2.1 (S), Q2.2 (S), Q2.3 (S), R34.1, R35.2, R37.2
GND: C29.2, F2.1, R18.2, R20.1
unnamed: C9.1, C10.2
unnamed: C28.2, C29.1
unnamed: D1.2 (A), Q2.5 (D), Q3.5 (D)
unnamed: D1.1 (K), R23.1
unnamed: D2.1 (K), R30.1
unnamed: D3.2 (A), F1.2, Q3.1 (S), Q3.2 (S), Q3.3 (S), R31.1
unnamed: D3.1 (K), Q3.4 (G), R31.2, R32.2
unnamed: D4.1 (K), Q2.4 (G), R33.2, R34.2
unnamed: J1.2, R2.1
unnamed: J1.3, R3.1
unnamed: J1.4, R4.1
unnamed: J1.5, R5.1
unnamed: J1.6, R6.1
unnamed: J1.7, R7.1
unnamed: J1.8, R8.1
unnamed: J1.9, R9.1
unnamed: J1.10, R10.1
unnamed: J1.11, R11.1
unnamed: J1.12, R12.1
unnamed: J1.13, R13.1
unnamed: J1.14, R14.1
unnamed: J1.15, R15.1
unnamed: J1.16, R16.1
unnamed: J2.2, TP1.1 (1_1), U1.21 (TS1)
unnamed: J3.2, TP2.1 (1_1), U1.22 (TS2/WAKE)
unnamed: J4.2, TP3.1 (1_1), U1.23 (TS3)
unnamed: Q1.2 (B), R22.2, U1.37 (BREG)
unnamed: C20.1, Q1.1 (C), R23.2
unnamed: R35.1, R36.2
unnamed: R37.1, R38.2
unnamed: C25.1, C26.1, C27.1, R30.2, U1.47 (BAT)
unnamed: R27.2, U1.29 (CFETOFF/SPI_CS)
unnamed: R32.1, U1.45 (CHG)
unnamed: C27.2, U1.46 (CP1)
unnamed: R29.2, U1.30 (DFETOFF/BOTHOFF)
unnamed: R33.1, U1.43 (DSG)
unnamed: R28.2, U1.28 (HDQ_IO/SPI_MOSI)
unnamed: R38.1, U1.41 (LD)
unnamed: R36.1, U1.42 (PACK)
unnamed: C1.1, R1.2, U1.16 (VC0)
unnamed: C2.1, C3.2, R2.2, U1.15 (VC1)
unnamed: C3.1, C4.2, R3.2, U1.14 (VC2)
unnamed: C4.1, C5.2, R4.2, U1.13 (VC3)
unnamed: C5.1, C6.2, R5.2, U1.12 (VC4)
unnamed: C6.1, C7.2, R6.2, U1.11 (VC5)
unnamed: C7.1, C8.2, R7.2, U1.10 (VC6)
unnamed: C8.1, C9.2, R8.2, U1.9 (VC7)
unnamed: R9.2, U1.8 (VC8)
unnamed: C10.1, C11.2, R10.2, U1.7 (VC9)
unnamed: C11.1, C12.2, R11.2, U1.6 (VC10)
unnamed: C12.1, C13.2, R12.2, U1.5 (VC11)
unnamed: C13.1, C14.2, R13.2, U1.4 (VC12)
unnamed: C14.1, C15.2, R14.2, U1.3 (VC13)
unnamed: C15.1, C16.2, R15.2, U1.2 (VC14)
unnamed: C16.1, C17.2, R16.2, U1.1 (VC15)
unnamed: C17.1, R17.2, U1.48 (VC16)
REG1: C21.1, R24.2, R25.2, R26.2, U1.35 (REG1)
REG2: C22.1, U1.34 (REG2)
RST: R21.1, U1.33 (RST_SHUT)
SCL: R25.1, U1.26 (SCL/SPI_CLK)
SDA: R24.1, U1.27 (SDA/SPI_MISO)
VSS: C1.2, C2.2, C20.2, C21.2, C22.2, C23.2, C24.2, C25.2, C26.2, J2.1, J3.1, J4.1, R21.2, R22.1, R27.1, R28.1, R29.1, U1.17 (VSS)
